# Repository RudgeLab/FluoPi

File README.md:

# [][website] 

Hardware design files, code and teaching materials for a low cost and open source fluorescent image registration station.

## Overview

FluoPi is composed of a blue-light transilluminator, an amber acrylic filter and a raspberry camera contained in a black acrylic mainframe. All the hardware is controlled with a Raspberry pi small computer.
With this equipment you are able to:  

* Take images of fluorescent samples ranges from um to cm.
* Perform timelapse assays of up to 3 fluorescent proteins simultaneously
* See electrophoresis gel stained with blue excitable chemicals (such as GelRed or SYBR Safe).

## Getting Started

You can see the full project at [OSF](https://osf.io/dy6p2/)
and a pre-print manuscript at [Biorxiv](https://www.biorxiv.org/content/early/2017/09/27/194324) and peer-reviewed article in [PLoS](http://journals.plos.org/plosone/article?id=10.1371/journal.pone.0187163)

### Prerequisites

To assemble this device you need access to a laser cutter and a 3D printer. You also need a mouse, keyboard and a screen
with HDMI (or hdmi to VGA adaptor) to connect with the Raspberry pi (you can also manage the equipment through SSH or using programs such as [teamviewer](https://pages.teamviewer.com/published/raspberrypi/))

### Installing

- All the installation instructions are available on the [wiki page][wiki]
- Full documentation and assembly instructions can be found at [Docubricks](http://docubricks.com/viewer.jsp?id=7449430440606889984)
  - If you are prompted regarding an https (SSL) error, proceed.

### Running the equipment

The equipment has a manual switch and the camera can be controlled with [_camera module commands_](https://www.raspberrypi.org/documentation/usage/camera/raspicam/README.md).
The project includes some python codes (based on [camera python module](https://www.raspberrypi.org/documentation/usage/camera/python/)) to control the hardware:  
* _timelapse.py_ --> to perform timelapse experiments
* _turnON.py_ --> to turn ON the transilluminator
* _turnOFF.py_ --> to turn OFF the transilluminator

### Running the notebooks

Jupyter notebooks are included (Examples/ and Tutorials/) to demonstrate the analysis principles and the use of the fluopi module to analyse time-lapse image data. Sample image data is included in the relevant folders. You can start from these examples, switching the file paths to your data.

## Authors

**Universidad Catolica de Chile**
* Isaac Nuñez - [Prosimio](https://github.com/Prosimio)
* Tamara Matute - [tfmatute](https://github.com/tfmatute)
* Juan Keymner - [Keymer Lab](http://keymerlab.nl/www/?page_id=26)
* Tim Rudge - [Rudge lab](http://rudge-lab.org)
* Fernan Federici - [Federici lab](https://federicilab.org)

[**Backyard Brains Chile**](http://www.backyardbrains.cl/)
* Roberto Pellizzari - [RoHPellizzari](https://github.com/RoHPellizzari)
* Tim Marzullo - [Backyard Brains](http://www.backyardbrains.cl/)

## License

This project is licensed under the MIT License - see the [LICENSE.txt](LICENSE.txt) file for details. Hardware is lincesed under the CERN license.

## FAQs and updates 
Please follow updates, ask questions and check FAQs in this [doc](https://docs.google.com/document/d/1-tSU8xBUZicgM2oZv8TOGw7QUYI85IWkbmjetRthfG8/edit?usp=sharing)

## Acknowledgments

* _Toby Wenzel_ for guidance on Docubricks documentation
* _Tom Baden_  and _Andre Chagas_ for feedback and advice on camera
* _Bernardo Pollak_ for helping out with sequences
* _Douglas Densmore_ for the CIDAR MoClo Parts Kit

* _OpenPlant Fund_ and _Fondecyt_ for providing financial support

[wiki]: https://github.com/SynBioUC/FluoPi/wiki
[website]: https://osf.io/dy6p2/

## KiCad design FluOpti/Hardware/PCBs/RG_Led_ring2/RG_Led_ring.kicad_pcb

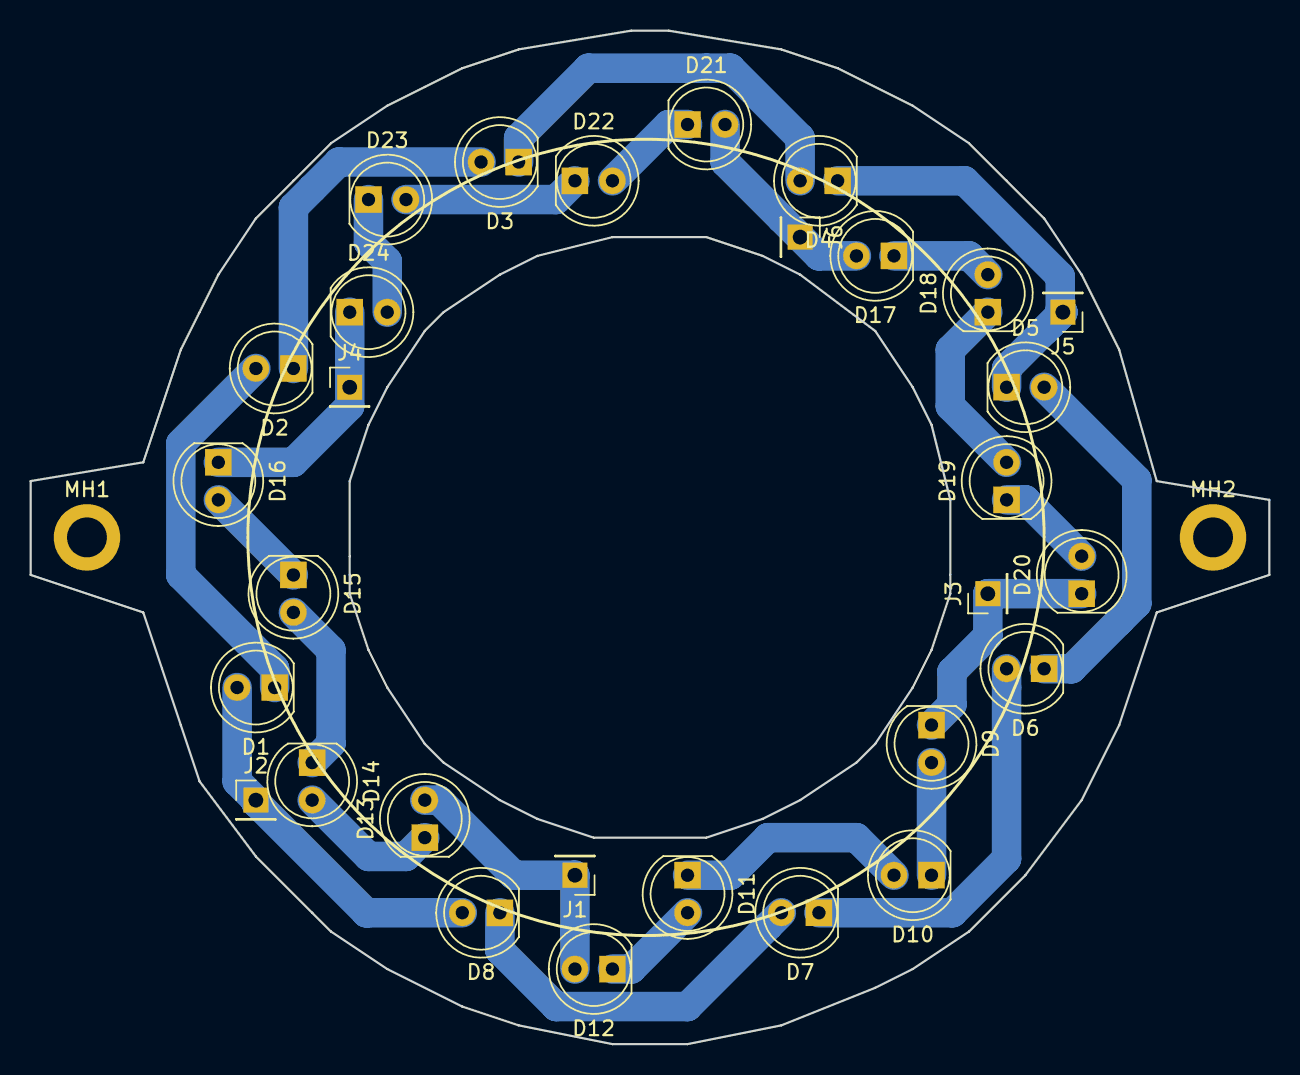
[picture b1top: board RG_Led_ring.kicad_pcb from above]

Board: 2 copper layers, 83.8 x 68.6 mm, 32 parts (0 on the bottom side), 24 nets.

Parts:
D1, D2, D3, D4, D5, D6, D7, D8, D9, D10, D11, D12, D13, D14, D15, D16, D17, D18, D19, D20, D21, D22, D23, D24: LED; LED_D5.0mm_FlatTop
J1, J2, J3, J4, J5, J6: Conn_01x01_Female; PinHeader_1x01_P2.54mm_Vertical
MH1, MH2: MountingHole; MountingHole_2.7mm_M2.5_ISO14580_Pad

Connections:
unnamed: D1.1, D2.2
unnamed: D1.2, D8.2, J2.1
unnamed: D2.1, D3.2
unnamed: D3.1, D4.2
unnamed: D4.1, D5.1, J5.1
unnamed: D5.2, D6.1
unnamed: D6.2, D7.1
unnamed: D7.2, D8.1
unnamed: D9.2, D10.1
unnamed: D10.2, D11.1
unnamed: D11.2, D12.1
unnamed: D12.2, D13.2, J1.1
unnamed: D13.1, D14.2
unnamed: D14.1, D15.2
unnamed: D15.1, D16.2
unnamed: D16.1, D24.1, J4.1
unnamed: D17.1, D18.2
unnamed: D17.2, D21.2, J6.1
unnamed: D18.1, D19.2
unnamed: D19.1, D20.2
unnamed: D9.1, D20.1, J3.1
unnamed: D21.1, D22.2
unnamed: D22.1, D23.2
unnamed: D23.1, D24.2

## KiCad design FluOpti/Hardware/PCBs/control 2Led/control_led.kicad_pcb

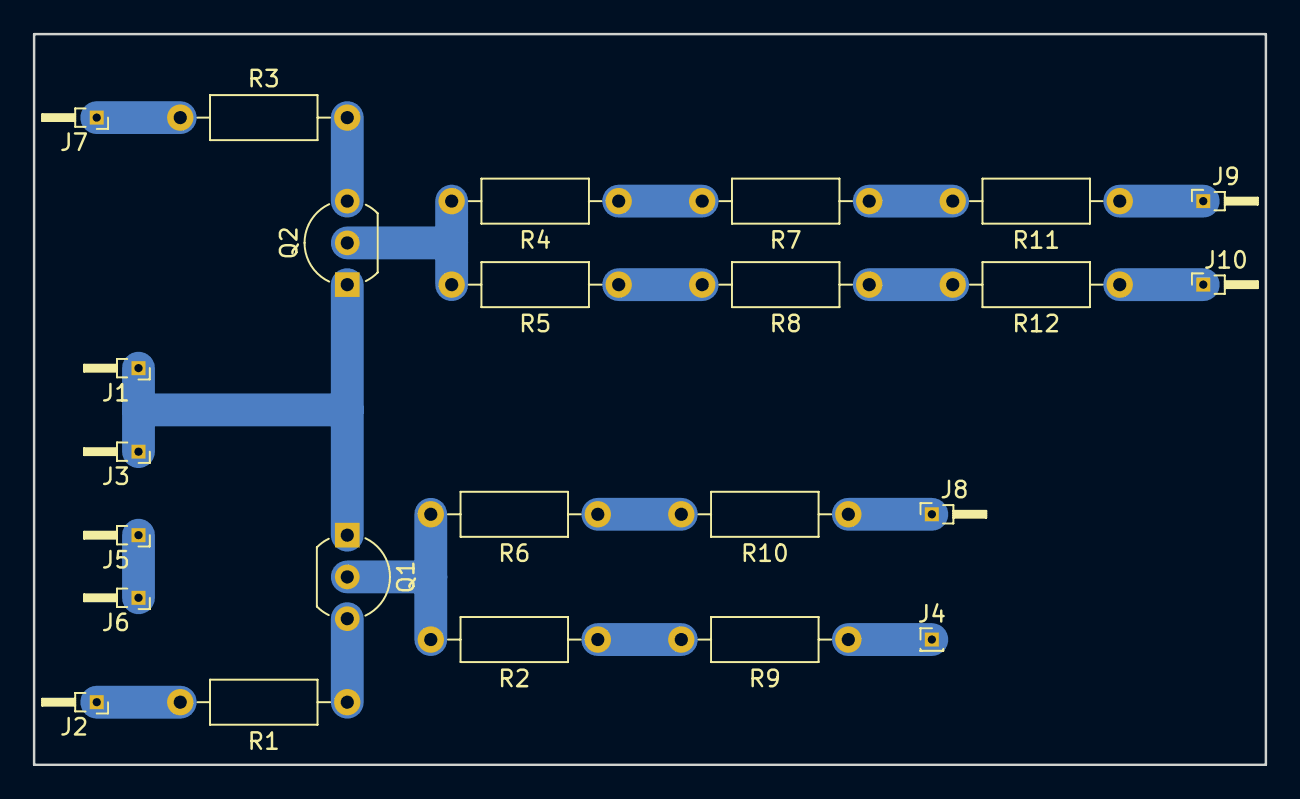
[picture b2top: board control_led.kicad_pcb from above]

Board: 2 copper layers, 74.9 x 44.5 mm, 24 parts (0 on the bottom side), 18 nets.

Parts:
J1, J2, J3, J5, J6, J7, J8, J9, J10: Conn_01x01_Female; PinHeader_1x01_P1.00mm_Horizontal
J4: Conn_01x01_Female; PinHeader_1x01_P1.00mm_Vertical
Q1: PN2222A; TO-92_Inline_Wide
Q2: 2N3904; TO-92_Inline_Wide
R1, R2, R3, R4, R5, R6, R7, R8, R9, R10, R11, R12: R; R_Axial_DIN0207_L6.3mm_D2.5mm_P10.16mm_Horizontal

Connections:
unnamed: J1.1, J3.1, Q1.1, Q2.1
unnamed: J2.1, R1.2
unnamed: J4.1, R9.1
unnamed: J5.1, J6.1
unnamed: J7.1, R3.1
unnamed: J8.1, R10.1
unnamed: J9.1, R11.1
unnamed: J10.1, R12.1
unnamed: Q1.2, R2.2, R6.2
unnamed: Q1.3, R1.1
unnamed: Q2.2, R4.2, R5.2
unnamed: Q2.3, R3.2
unnamed: R2.1, R9.2
unnamed: R4.1, R7.2
unnamed: R5.1, R8.2
unnamed: R6.1, R10.2
unnamed: R7.1, R11.2
unnamed: R8.1, R12.2

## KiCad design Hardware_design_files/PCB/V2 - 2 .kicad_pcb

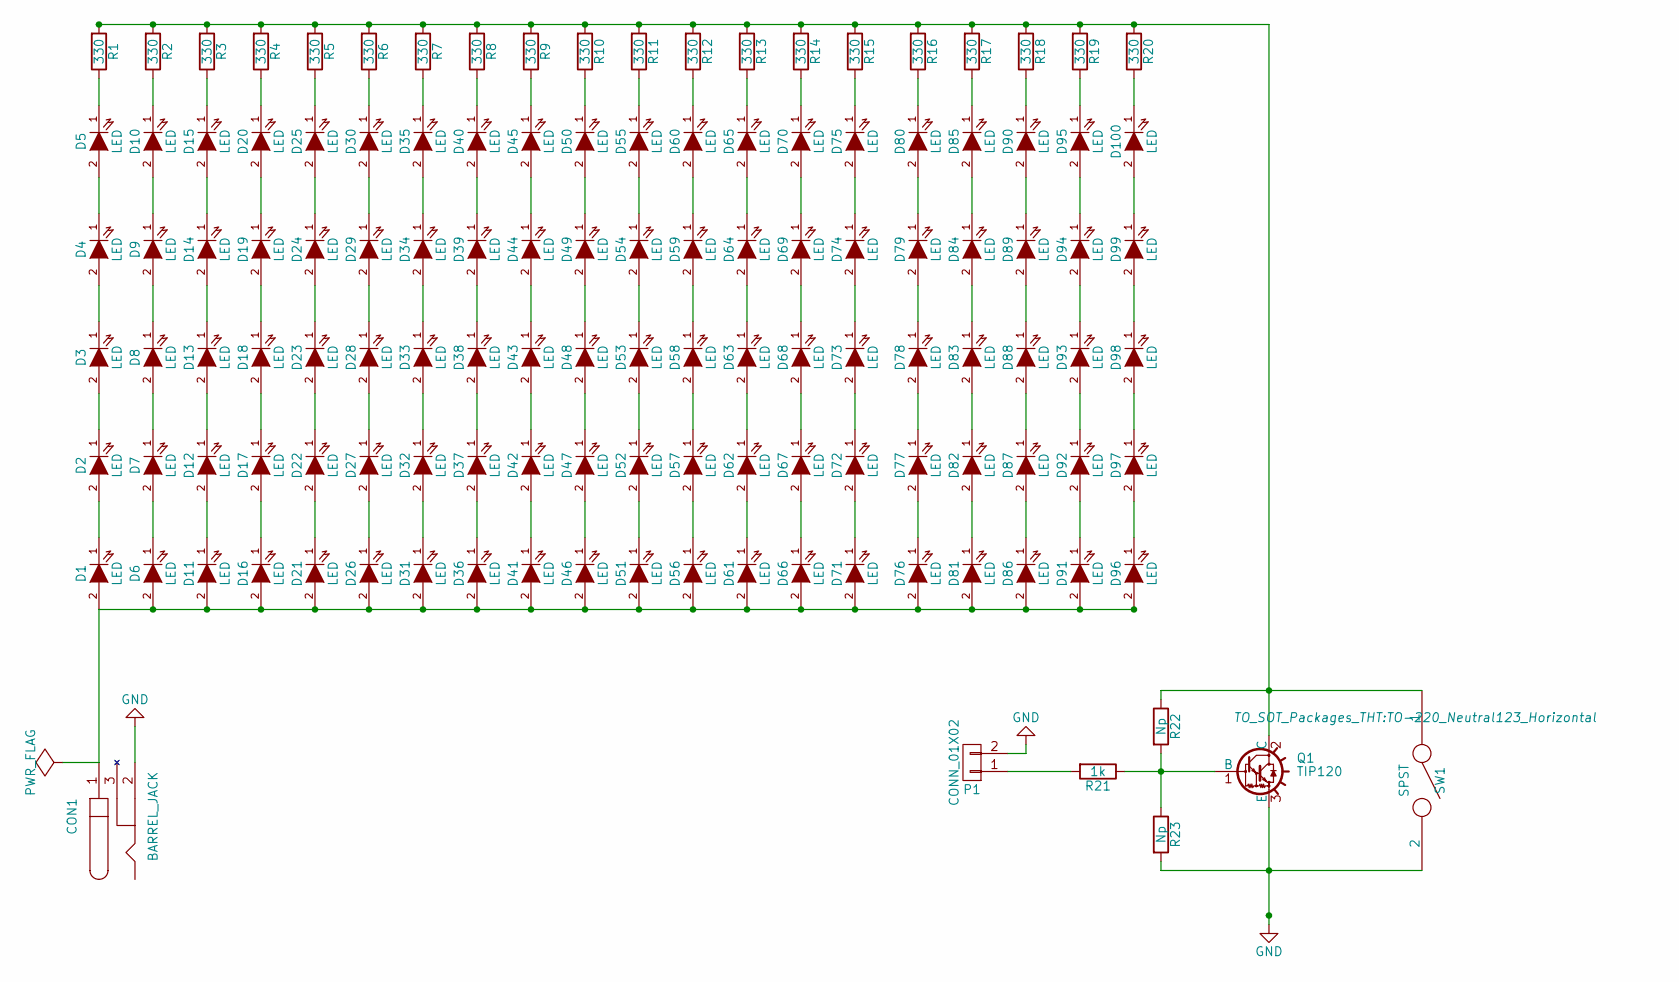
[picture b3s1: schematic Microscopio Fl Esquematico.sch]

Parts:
CON1: BARREL_JACK
D1, D2, D3, D4, D5, D6, D7, D8, D9, D10, D11, D12, D13, D14, D15, D16, D17, D18, D19, D20, D21, D22, D23, D24, D25, D26, D27, D28, D29, D30, D31, D32, D33, D34, D35, D36, D37, D38, D39, D40, D41, D42, D43, D44, D45, D46, D47, D48, D49, D50, D51, D52, D53, D54, D55, D56, D57, D58, D59, D60, D61, D62, D63, D64, D65, D66, D67, D68, D69, D70, D71, D72, D73, D74, D75, D76, D77, D78, D79, D80, D81, D82, D83, D84, D85, D86, D87, D88, D89, D90, D91, D92, D93, D94, D95, D96, D97, D98, D99, D100: LED; LED-5MM
P1: CONN_01X02; Pin_Header_Straight_1x02
Q1: TIP120; TO-220_Neutral123_Horizontal
R1, R2, R3, R4, R5, R6, R7, R8, R9, R10, R11, R12, R13, R14, R15, R16, R17, R18, R19, R20: 330; Resistor_Horizontal_RM7mm
R21: 1k; Resistor_Horizontal_RM7mm
R22, R23: Np; Resistor_Horizontal_RM7mm
SW1: SPST; SW_DIP_x1_Slide

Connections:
GND: CON1.2, P1.2, Q1.3 (E), R23.2, SW1.2
unnamed: CON1.1, D1.2 (A), D6.2 (A), D11.2 (A), D16.2 (A), D21.2 (A), D26.2 (A), D31.2 (A), D36.2 (A), D41.2 (A), D46.2 (A), D51.2 (A), D56.2 (A), D61.2 (A), D66.2 (A), D71.2 (A), D76.2 (A), D81.2 (A), D86.2 (A), D91.2 (A), D96.2 (A)
unnamed: D1.1 (K), D2.2 (A)
unnamed: D2.1 (K), D3.2 (A)
unnamed: D3.1 (K), D4.2 (A)
unnamed: D4.1 (K), D5.2 (A)
unnamed: D5.1 (K), R1.1
unnamed: D6.1 (K), D7.2 (A)
unnamed: D7.1 (K), D8.2 (A)
unnamed: D8.1 (K), D9.2 (A)
unnamed: D10.1 (K), R2.1
unnamed: D9.1 (K), D10.2 (A)
unnamed: D11.1 (K), D12.2 (A)
unnamed: D12.1 (K), D13.2 (A)
unnamed: D13.1 (K), D14.2 (A)
unnamed: D14.1 (K), D15.2 (A)
unnamed: D15.1 (K), R3.1
unnamed: D16.1 (K), D17.2 (A)
unnamed: D17.1 (K), D18.2 (A)
unnamed: D18.1 (K), D19.2 (A)
unnamed: D19.1 (K), D20.2 (A)
unnamed: D20.1 (K), R4.1
unnamed: D21.1 (K), D22.2 (A)
unnamed: D22.1 (K), D23.2 (A)
unnamed: D23.1 (K), D24.2 (A)
unnamed: D24.1 (K), D25.2 (A)
unnamed: D25.1 (K), R5.1
unnamed: D26.1 (K), D27.2 (A)
unnamed: D27.1 (K), D28.2 (A)
unnamed: D28.1 (K), D29.2 (A)
unnamed: D29.1 (K), D30.2 (A)
unnamed: D30.1 (K), R6.1
unnamed: D31.1 (K), D32.2 (A)
unnamed: D32.1 (K), D33.2 (A)
unnamed: D33.1 (K), D34.2 (A)
unnamed: D34.1 (K), D35.2 (A)
unnamed: D35.1 (K), R7.1
unnamed: D36.1 (K), D37.2 (A)
unnamed: D37.1 (K), D38.2 (A)
unnamed: D38.1 (K), D39.2 (A)
unnamed: D39.1 (K), D40.2 (A)
unnamed: D40.1 (K), R8.1
unnamed: D41.1 (K), D42.2 (A)
unnamed: D42.1 (K), D43.2 (A)
unnamed: D43.1 (K), D44.2 (A)
unnamed: D44.1 (K), D45.2 (A)
unnamed: D45.1 (K), R9.1
unnamed: D46.1 (K), D47.2 (A)
unnamed: D47.1 (K), D48.2 (A)
unnamed: D48.1 (K), D49.2 (A)
unnamed: D49.1 (K), D50.2 (A)
unnamed: D50.1 (K), R10.1
unnamed: D51.1 (K), D52.2 (A)
unnamed: D52.1 (K), D53.2 (A)
unnamed: D53.1 (K), D54.2 (A)
unnamed: D54.1 (K), D55.2 (A)
unnamed: D55.1 (K), R11.1
unnamed: D56.1 (K), D57.2 (A)
unnamed: D57.1 (K), D58.2 (A)
unnamed: D58.1 (K), D59.2 (A)
unnamed: D59.1 (K), D60.2 (A)
unnamed: D60.1 (K), R12.1
unnamed: D61.1 (K), D62.2 (A)
unnamed: D62.1 (K), D63.2 (A)
unnamed: D63.1 (K), D64.2 (A)
unnamed: D64.1 (K), D65.2 (A)
unnamed: D65.1 (K), R13.1
unnamed: D66.1 (K), D67.2 (A)
unnamed: D67.1 (K), D68.2 (A)
unnamed: D68.1 (K), D69.2 (A)
unnamed: D69.1 (K), D70.2 (A)
unnamed: D70.1 (K), R14.1
unnamed: D71.1 (K), D72.2 (A)
unnamed: D72.1 (K), D73.2 (A)
unnamed: D73.1 (K), D74.2 (A)
unnamed: D74.1 (K), D75.2 (A)
unnamed: D75.1 (K), R15.1
unnamed: D76.1 (K), D77.2 (A)
unnamed: D77.1 (K), D78.2 (A)
unnamed: D78.1 (K), D79.2 (A)
unnamed: D79.1 (K), D80.2 (A)
unnamed: D80.1 (K), R16.1
unnamed: D81.1 (K), D82.2 (A)
unnamed: D82.1 (K), D83.2 (A)
unnamed: D83.1 (K), D84.2 (A)
unnamed: D84.1 (K), D85.2 (A)
unnamed: D85.1 (K), R17.1
unnamed: D86.1 (K), D87.2 (A)
unnamed: D87.1 (K), D88.2 (A)
unnamed: D88.1 (K), D89.2 (A)
unnamed: D89.1 (K), D90.2 (A)
unnamed: D90.1 (K), R18.1
unnamed: D91.1 (K), D92.2 (A)
unnamed: D92.1 (K), D93.2 (A)
unnamed: D93.1 (K), D94.2 (A)
unnamed: D94.1 (K), D95.2 (A)
unnamed: D95.1 (K), R19.1
unnamed: D96.1 (K), D97.2 (A)
unnamed: D97.1 (K), D98.2 (A)
unnamed: D98.1 (K), D99.2 (A)
unnamed: D100.1 (K), R20.1
unnamed: D99.1 (K), D100.2 (A)
unnamed: P1.1, R21.2
unnamed: Q1.1 (B), R21.1, R22.2, R23.1
unnamed: Q1.2 (C), R1.2, R2.2, R3.2, R4.2, R5.2, R6.2, R7.2, R8.2, R9.2, R10.2, R11.2, R12.2, R13.2, R14.2, R15.2, R16.2, R17.2, R18.2, R19.2, R20.2, R22.1, SW1.1

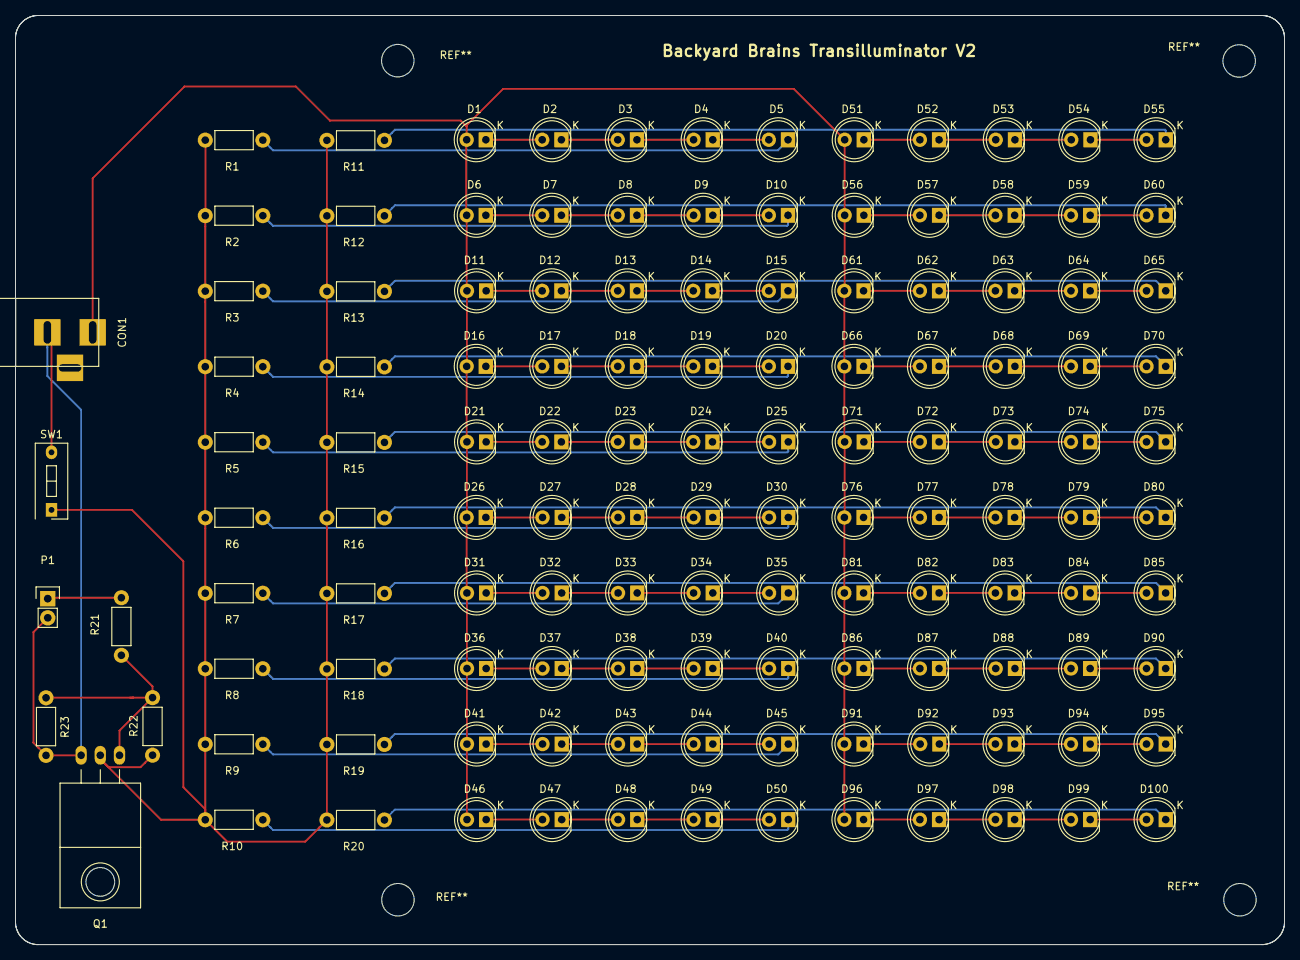
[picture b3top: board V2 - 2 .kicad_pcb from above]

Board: 2 copper layers, 168.0 x 123.0 mm, 127 parts (0 on the bottom side), 105 nets.

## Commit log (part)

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2016-11-21 Update to newer code without previews and some better camera settings. Also attempt to use matplotlib in notebook.
2016-11-21 Add more explanatory text and try plotting with matplotlib
2016-11-21 Minor edits, inline plotting now works after installing tk, python-tk etc.
2016-11-21 Very minor cleanup
2016-11-29 Python script from raspi that runs simple timelapse loop
2016-11-29 Split python code into blocks for explanation
2016-11-30 Not sure what I did...
2016-12-21 Timelapse with new settings for the camera
2017-01-07 Simple image processing steps
2017-01-08 Image processing
2017-01-09 More plotting and looking at correlations
2017-01-18 Attempting to track area growth of colonies
2017-01-18 Add TL1 and TL2 to gitignore so they dont get committed again by mistake
2017-01-19 inicial download commit
2017-01-19 timelapse 13_1_17 code
2017-01-27 Analysis of radius growth
2017-01-27 Tidy up
2017-01-28 Check radius estimate against intensity profile
2017-01-28 Explanatory text added
2017-01-29 Add diagram for image array structure
2017-01-29 Diagram for timeseries array structure, edit explanatory text
2017-01-29 Add links to documentation and turorials
2017-01-29 Cut down to use on every 10th frame for speed. More comments. Plot outputs now back in notebook.
2017-01-29 ROI timelapse output to image series, for video creation
2017-01-31 Minor changes
2017-02-11 Spline smoothing of data and computation of expression rate
2017-03-06 Create BOM
2017-03-06 2D Files
    Laser Cut Files for Production
2017-03-06 Create 3D Files
2017-03-06 Create Electronics
2017-03-06 Create pdfs
2017-03-07 Create Assembly instructions
2017-03-12 add some generalizations on the code together with some visualization of the desitions taken on the analysis
2017-03-12 Color profile relation analysis added
2017-03-13 linear fitting of gren/blue ratios added
2017-03-20 Add files via upload
    Corrección de assembly instructions
2017-03-22 new notebook added: Color Analysis. This notebook is to get the color profiles for the different bacterial strains
2017-03-24 General color analysis added: This mean, Green v/s Red profiles in the whole image over time
2017-03-24 main channel identification and smooth over all the channels was included
2017-03-24 colony identification included
2017-03-24 rois and circular colony area inside each rois identified
2017-04-06 channel plot corrected. ROIS out of boundaries corrected. Last time channel plot added
2017-04-07 linear fit included
2017-04-18 end time point color analisys ready
2017-05-05 Update Docubricks
2017-05-05 Rename Docubricks to Info
2017-05-10 Nothing really
2017-05-16 Upload assembly instructions for the top module.
2017-05-18 background computation ready
2017-05-19 include background identification, computation and substracition
2017-05-19 include blob (colony) detection
2017-05-19 include fluoresce and growth data extraction
2017-05-30 module with some useful functions to analyse data
2017-05-31 new file for colony clasification (to replace color analysis). it only laks some text: explanation + maths
2017-06-28 Simplifying and expanding text.
2017-07-03 Full notebooks added. These notebooks are not tutorials, instead are to perform more complete analysis in a compact and complete way
2017-07-03 Full Color Analysis added
2017-07-05 correct some future deprecated functions on the code. Explore the radio obtention for each time along with the different ways to estimate k(t)
2017-07-12 Edit and add to comments
2017-07-13 Reorganising and cleaning up old files
2017-07-13 Modules structure for common functions. Moved to FluoPi (temporary name)
2017-07-13 Reorganising files
2017-07-13 Renaming files consistently
2017-07-13 Remove duplicate files
2017-07-13 some functions where corrected and some comments where added
2017-07-13 Rename module with the functions (RaspFunctions) as FluoPi_Fucntions
2017-07-13 Edit tutorial for controlling hardware and doing timelapse
2017-07-13 Minor edits
2017-07-14 Put module functions in __init__.py so that they are at the top level of the module, i.e. FluoPi.func()
2017-07-14 Make tutorial work with timelapse TLE_G_7_3_17
2017-07-14 Changing module name to lower case, first have to remove
2017-07-14 Module now with lowercase names
2017-07-14 Actualice the function colonyBlob
2017-07-14 Change path to data
2017-07-14 Moving example notebook to use fluopi module (not finished)
2017-07-14 Actualice details on some functions and finish the comments on everyone
2017-07-14 really nothing on examples... only to pull
2017-07-14 add CRoiMeanInt_frames function to get the I/A value of colony at each time
2017-07-14 add growth rate computation function
2017-07-14 generalize somethings on the module
2017-07-15 add corrections to the module, and probe it on Colony_size_and_fluo_full
2017-07-17 module complete for functions used on Colony_size_and_fluo_full example
2017-07-18 Fix some calls to fluopi module
2017-07-19 Add some plots to Examples Colony size and fluo full, and correct some details on the module
2017-07-20 generalize the fitting funtion to fit different arrays and use different functions
2017-07-20 changes the fitting from the radius to the area to improve the meaning of the parameters
2017-07-20 add some plot
2017-07-20 add Plots/ folder
2017-08-03 Create Info
2017-08-03 Create 3D
2017-08-03 Add files for 3d printing
2017-08-21 Updated authors
2017-09-06 Create 3dfiles
2017-09-06 Replaced 3d files for printing
2017-09-08 reorganization of 2D and 3D files
2017-09-08 Cleaning up the timelapse script
2017-09-08 Create folder for ready-to-cut files
2017-09-08 Added ready-to-cut files
2017-09-08 Create folder for ready to print files
2017-09-09 cost breakdown file added
2017-09-10 deleted repeated stl file
2017-09-13 Delete 0-0-0-0-0-0-0-0-5mm Blue LED - 470 nm - T1 3:4 LED w: 120 Degree Viewing Angle | Through Hole LEDs | Component LEDs | Super Bright LEDs.pdf
    name problems, I will fix and reload it
2017-09-13 Delete 0-0-0-0-0-0-0-5mm Blue LED - 470 nm - T1 3:4 LED w: 120 Degree Viewing Angle | Through Hole LEDs | Component LEDs | Super Bright LEDs.pdf
    filename problems, I will fix and reload it
2017-09-14 merging Colony classificator
2017-09-14 format corrected accord PEP8 until data_sum_time (included)
2017-09-15 complete the pep8 formatting and organize the functions correctly on the two defined categories
2017-09-20 Colony_size_and_fluo_full functions names corrected
2017-09-21 take some function from the colony_classification notebook and put them add them to the module. It include the proper explanation and docstrings of each function. Also, I perform the generalization o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
2017-09-21 perform some corrections on analysis/colony_classifier functionand also correct some format issues
2017-09-22 Jupyter notebooks where corrected and put up to date with the module functions
2017-09-22 add LICENCE and README files
2017-09-22 correct minor stuff on README.md
2017-09-23 make a more complete setup file -it lacks some things yet- and minnor stuff on README
2017-09-24 add some install requires
2017-09-25 Rename the files with shorter names
2017-09-27 change Parameters by Args
2017-09-27 change Args by Parameters, important to generate the docstrings
2017-09-27 add correctly Parameters section to the docs
2017-09-27 correct minor code stuff
2017-09-29 add the files with the matematical explanation of the data analysis presented in "Examples"
2017-09-29 minor formatting changes
2017-09-29 add a folder with images for the wiki
2017-09-30 readme corrections
2017-09-30 readme corrections at text and docubricks link
2017-09-30 readme corrections at text and docubricks link fix II
2017-10-03 Remove ipynb checkpoint files
2017-10-04 complete the requirements for the setup
2017-10-05 add some images used in the wiki
2017-10-05 complete the licence copyright
2017-10-05 Fix call to sys.argv
2017-10-05 Fix typo in setup.py
2017-10-05 Add datetime to file names, also fix some typos
2017-10-06 new image for wiki
2017-10-06 change the name of the example notebook
2017-10-06 make minor code corrections, clean some comments and specify the cycle printed information
2017-10-06 change the extension of some wiki images
2017-10-06 Build docs
2017-10-06 Remove docs build
2017-10-06 colony_classifier minor corrections
2017-10-06 RADME minor corrections
2017-10-06 minor changes to notebooks
2017-10-06 tutorial minor change
2017-10-06 minor language corrections
2017-10-08 removed plot holds from tutorial image_processing and make A int(round(A))
2017-10-08 add a note to tutorial operating fluopi
2017-10-09 add abspath
2017-10-09 add example image data
2017-10-09 add a new way of include the path name
2017-10-09 Plots folder re-organized
2017-10-09 minor change to fluopi analysis
2017-10-09 change the filename
2017-10-09 change filenames
2017-10-10 add comments, folder check and creation and args display
2017-10-10 remove duplicated timelapse.py file
2017-10-10 remove innecessary jupyter checkpoint folder
2017-10-10 remove old plots
2017-10-10 correct minor details and add explanations
2017-10-10 correct minor stuff on fluopi modules
2017-10-11 Correct roi plotting to get data from dict
2017-10-11 Cast index to integer
2017-10-11 Trying to fix chansum
2017-10-11 add some explanations and minor correction on parameters names
2017-10-11 Move sphinx doc files to sphinx
2017-10-11 Add html docs to docs folder
2017-10-11 add setup.cfg necessary to upload the module to PyPI
2017-10-12 add the tag release link to the setup file
2017-10-12 correct and add new classifiers
2017-10-12 correct the setup long description
2017-10-12 eliminate extra word
2017-10-13 fixing some page issues
2017-10-13 minor improvement and re-organization of the documentation page
2017-10-13 change the html theme from alabaster to classic
2017-10-30 Update timelapse.py
    Los dos puntos ":" usados en el time stamp del nombre de archivo no son válidos como nombre de archivo en sistemas no linux, así que se cambia por un guion bajo "_"
2018-01-31 add pic of FluoPi dimensions
2018-01-31 add dimensions
2018-03-09 acrylic bills added
2018-03-13 STLs and openscad files for new camera holder and M12 adapter
2018-03-13 added link to README
2018-03-13 updates.md added
2018-05-29 acrylics chart for similar blue filters added
2018-07-29 Added preview, Exif, update Timelapse
2018-07-29 add link to piCameraApp
2018-10-08 moved positive track away from screw hole, so that the screw does not damage it when placed in
2019-04-16 Add files via upload
    include a text file with manufacturing specifications (like material, thickness, etc)
2019-06-15 i) Improve the row transect function. ii) Include transect visualization as criteria to define the smoothing.iii) Modify the colony_bloobs_id function to receive the min and max sigma values as input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
2019-06-17 i) fix the radius computation formula. ii) fix check_radius function to manage properly the x-axis. iii) create ROI_radius function to improve the visualization of radii estimation
2019-06-17 tl_roi function was corrected to avoid inconsistenses with time vector v/s frame. Also more functionatilities were added and some computing redundance was eliminated
2019-06-26 modify get_im_data function. Now it is not compulsory to start the analysis from the first image serie but to start from any desired image
2019-07-09 Add a couple of funtions to store and load the analized data and parameters
2019-07-18 Minor updates for readability.
2019-10-04 minor modification to row transect plotting function to display a superior title over the whole figure
2020-03-30 camera holder design file and STLs for RPIv2 and Waveshare cameras were added
2020-03-30 circular filter holder and focus knob adapted to attach it were added. It means both design files and STLs for 3D printing
2021-09-03 This is the FluOpti upgrade folder with all the code, designs and sample experiments
2022-02-06 README: repair link to DocuBricks documentation
    - Previous link was a soft-404.
    - New link is valid: http://docubricks.com/viewer.jsp?id=7449430440606889984
